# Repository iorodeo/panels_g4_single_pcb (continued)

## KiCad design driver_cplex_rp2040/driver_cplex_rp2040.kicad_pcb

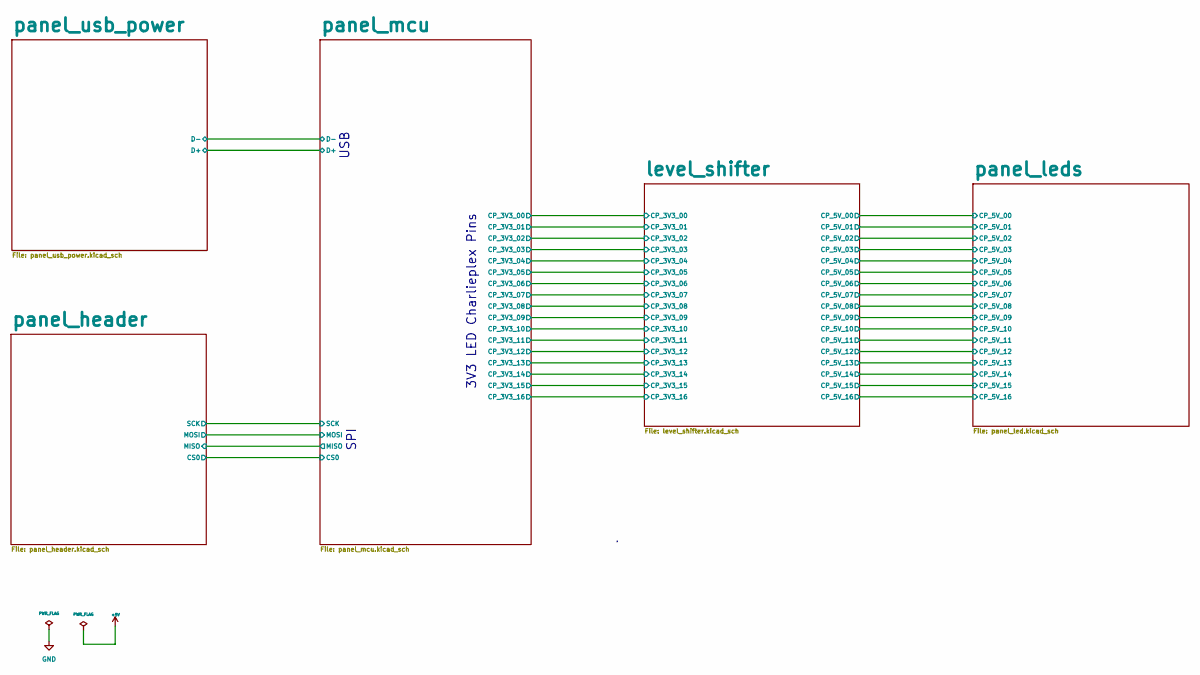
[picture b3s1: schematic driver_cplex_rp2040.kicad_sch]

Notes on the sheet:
SPI
USB
3V3 LED Charlieplex Pins

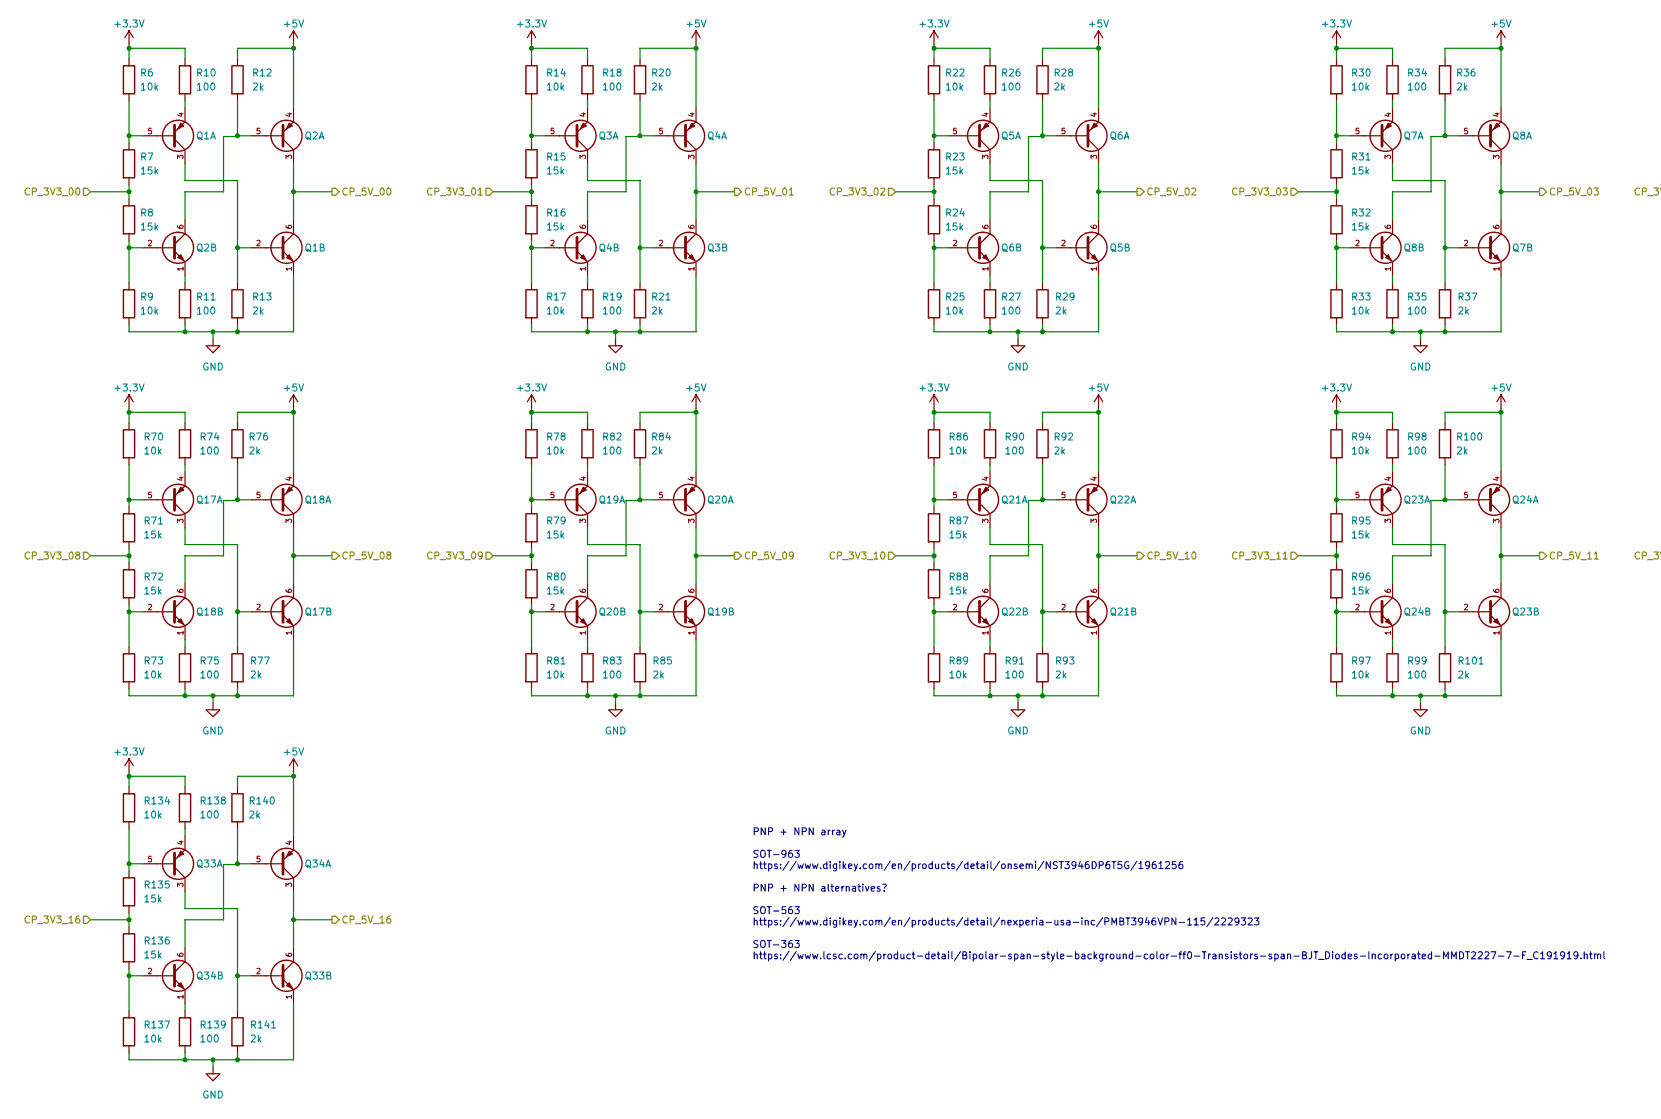
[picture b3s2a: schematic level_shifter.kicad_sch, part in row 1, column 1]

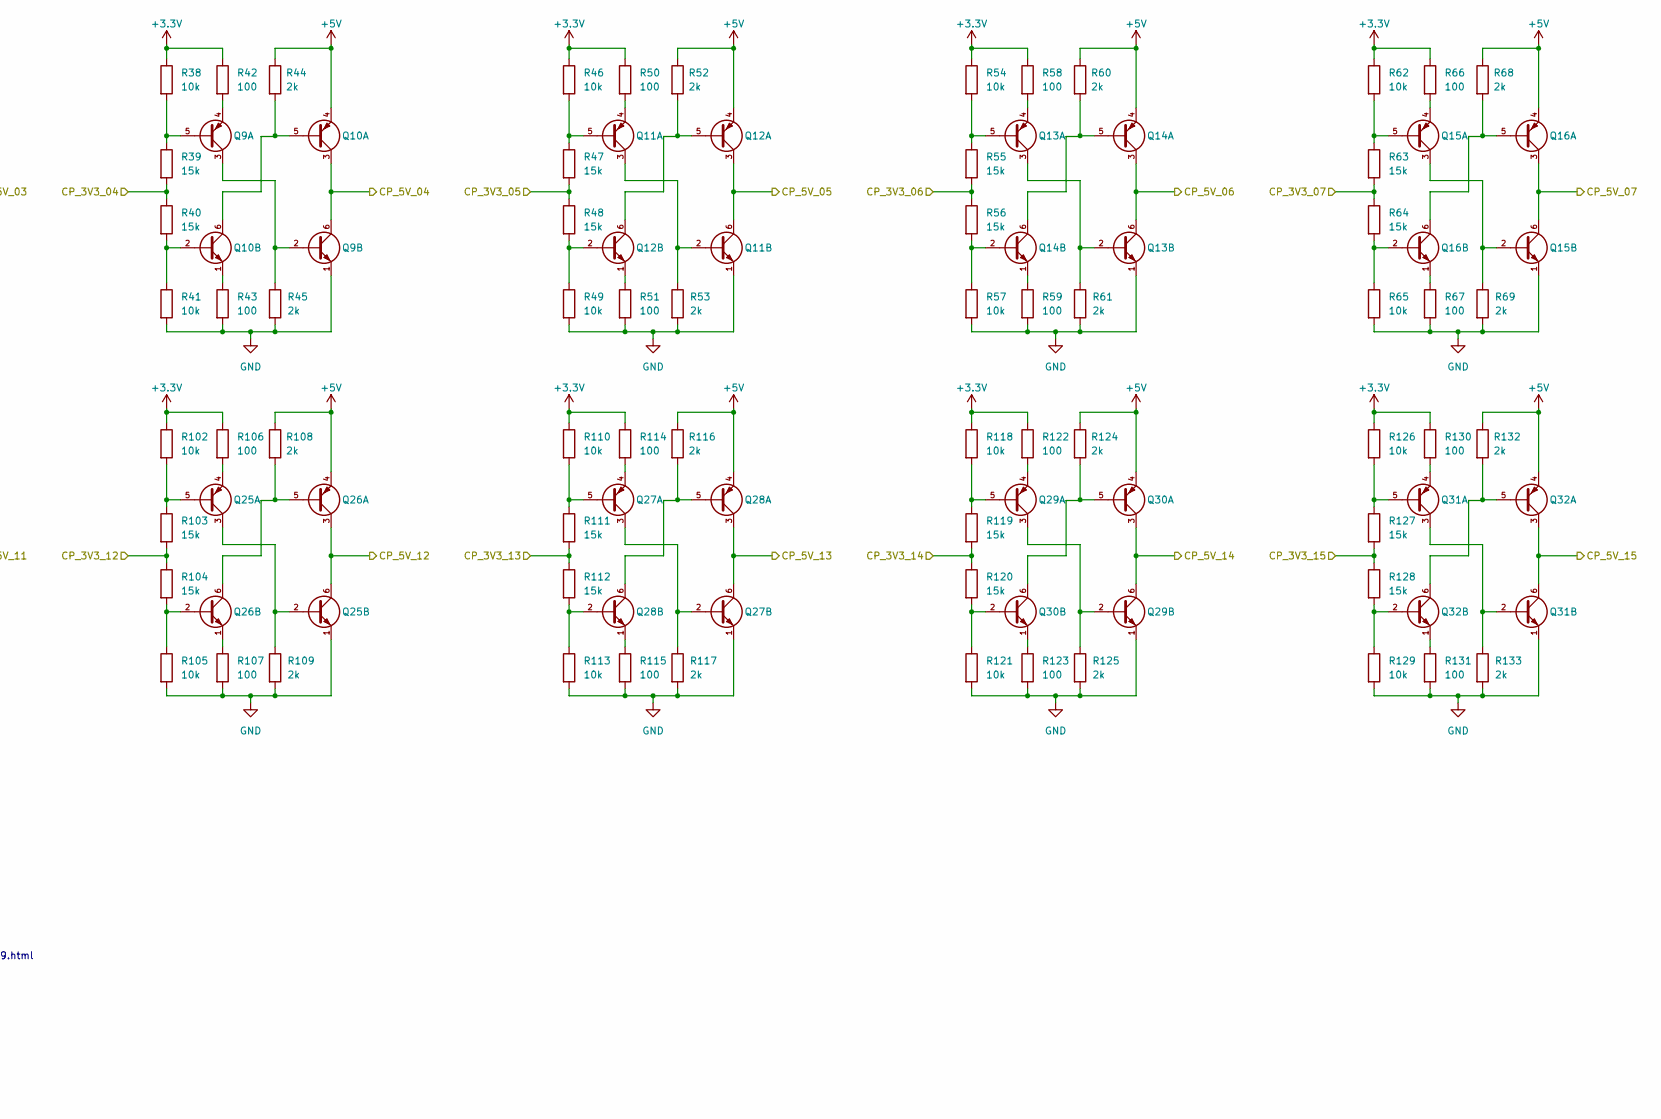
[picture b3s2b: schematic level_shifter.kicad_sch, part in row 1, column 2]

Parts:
Q1, Q2, Q3, Q4, Q5, Q6, Q7, Q8, Q9, Q10, Q11, Q12, Q13, Q14, Q15, Q16, Q17, Q18, Q19, Q20, Q21, Q22, Q23, Q24, Q25, Q26, Q27, Q28, Q29, Q30, Q31, Q32, Q33, Q34: 1xPNP and 1xNPN; SOT-963
R6, R9, R14, R17, R22, R25, R30, R33, R38, R41, R46, R49, R54, R57, R62, R65, R70, R73, R78, R81, R86, R89, R94, R97, R102, R105, R110, R113, R118, R121, R126, R129, R134, R137: 10k; R_0201_0603Metric
R7, R8, R15, R16, R23, R24, R31, R32, R39, R40, R47, R48, R55, R56, R63, R64, R71, R72, R79, R80, R87, R88, R95, R96, R103, R104, R111, R112, R119, R120, R127, R128, R135, R136: 15k; R_0201_0603Metric
R10, R11, R18, R19, R26, R27, R34, R35, R42, R43, R50, R51, R58, R59, R66, R67, R74, R75, R82, R83, R90, R91, R98, R99, R106, R107, R114, R115, R122, R123, R130, R131, R138, R139: 100; R_0201_0603Metric
R12, R13, R20, R21, R28, R29, R36, R37, R44, R45, R52, R53, R60, R61, R68, R69, R76, R77, R84, R85, R92, R93, R100, R101, R108, R109, R116, R117, R124, R125, R132, R133, R140, R141: 2k; R_0201_0603Metric

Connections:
+3.3V: R6.1, R10.1, R14.1, R18.1, R22.1, R26.1, R30.1, R34.1, R38.1, R42.1, R46.1, R50.1, R54.1, R58.1, R62.1, R66.1, R70.1, R74.1, R78.1, R82.1, R86.1, R90.1, R94.1, R98.1, R102.1, R106.1, R110.1, R114.1, R118.1, R122.1, R126.1, R130.1, R134.1, R138.1; also elsewhere on the board
+5V: Q2.4, Q4.4, Q6.4, Q8.4, Q10.4, Q12.4, Q14.4, Q16.4, Q18.4, Q20.4, Q22.4, Q24.4, Q26.4, Q28.4, Q30.4, Q32.4, Q34.4, R12.1, R20.1, R28.1, R36.1, R44.1, R52.1, R60.1, R68.1, R76.1, R84.1, R92.1, R100.1, R108.1, R116.1, R124.1, R132.1, R140.1; also elsewhere on the board
/level_shifter/CP_3V3_00: R7.2, R8.1; also elsewhere on the board
/level_shifter/CP_3V3_01: R15.2, R16.1; also elsewhere on the board
/level_shifter/CP_3V3_02: R23.2, R24.1; also elsewhere on the board
/level_shifter/CP_3V3_03: R31.2, R32.1; also elsewhere on the board
/level_shifter/CP_3V3_04: R39.2, R40.1; also elsewhere on the board
/level_shifter/CP_3V3_05: R47.2, R48.1; also elsewhere on the board
/level_shifter/CP_3V3_06: R55.2, R56.1; also elsewhere on the board
/level_shifter/CP_3V3_07: R63.2, R64.1; also elsewhere on the board
/level_shifter/CP_3V3_08: R71.2, R72.1; also elsewhere on the board
/level_shifter/CP_3V3_09: R79.2, R80.1; also elsewhere on the board
/level_shifter/CP_3V3_10: R87.2, R88.1; also elsewhere on the board
/level_shifter/CP_3V3_11: R95.2, R96.1; also elsewhere on the board
/level_shifter/CP_3V3_12: R103.2, R104.1; also elsewhere on the board
/level_shifter/CP_3V3_13: R111.2, R112.1; also elsewhere on the board
/level_shifter/CP_3V3_14: R119.2, R120.1; also elsewhere on the board
/level_shifter/CP_3V3_15: R127.2, R128.1; also elsewhere on the board
/level_shifter/CP_3V3_16: R135.2, R136.1; also elsewhere on the board
/level_shifter/CP_5V_00: Q1.6, Q2.3; also elsewhere on the board
/level_shifter/CP_5V_01: Q3.6, Q4.3; also elsewhere on the board
/level_shifter/CP_5V_02: Q5.6, Q6.3; also elsewhere on the board
/level_shifter/CP_5V_03: Q7.6, Q8.3; also elsewhere on the board
/level_shifter/CP_5V_04: Q9.6, Q10.3; also elsewhere on the board
/level_shifter/CP_5V_05: Q11.6, Q12.3; also elsewhere on the board
/level_shifter/CP_5V_06: Q13.6, Q14.3; also elsewhere on the board
/level_shifter/CP_5V_07: Q15.6, Q16.3; also elsewhere on the board
/level_shifter/CP_5V_08: Q17.6, Q18.3; also elsewhere on the board
/level_shifter/CP_5V_09: Q19.6, Q20.3; also elsewhere on the board
/level_shifter/CP_5V_10: Q21.6, Q22.3; also elsewhere on the board
/level_shifter/CP_5V_11: Q23.6, Q24.3; also elsewhere on the board
/level_shifter/CP_5V_12: Q25.6, Q26.3; also elsewhere on the board
/level_shifter/CP_5V_13: Q27.6, Q28.3; also elsewhere on the board
/level_shifter/CP_5V_14: Q29.6, Q30.3; also elsewhere on the board
/level_shifter/CP_5V_15: Q31.6, Q32.3; also elsewhere on the board
/level_shifter/CP_5V_16: Q33.6, Q34.3; also elsewhere on the board
GND: Q1.1, Q3.1, Q5.1, Q7.1, Q9.1, Q11.1, Q13.1, Q15.1, Q17.1, Q19.1, Q21.1, Q23.1, Q25.1, Q27.1, Q29.1, Q31.1, Q33.1, R9.2, R11.2, R13.2, R17.2, R19.2, R21.2, R25.2, R27.2, R29.2, R33.2, R35.2, R37.2, R41.2, R43.2, R45.2, R49.2, R51.2, R53.2, R57.2, R59.2, R61.2, R65.2, R67.2, R69.2, R73.2, R75.2, R77.2, R81.2, R83.2, R85.2, R89.2, R91.2, R93.2, R97.2, R99.2, R101.2, R105.2, R107.2, R109.2, R113.2, R115.2, R117.2, R121.2, R123.2, R125.2, R129.2, R131.2, R133.2, R137.2, R139.2, R141.2; also elsewhere on the board
unnamed: Q1.2, Q1.3, R13.1
unnamed: Q1.4, R10.2
unnamed: Q1.5, R6.2, R7.1
unnamed: Q2.1, R11.1
unnamed: Q2.2, R8.2, R9.1
unnamed: Q2.5, Q2.6, R12.2
unnamed: Q3.2, Q3.3, R21.1
unnamed: Q3.4, R18.2
unnamed: Q3.5, R14.2, R15.1
unnamed: Q4.1, R19.1
unnamed: Q4.2, R16.2, R17.1
unnamed: Q4.5, Q4.6, R20.2
unnamed: Q5.2, Q5.3, R29.1
unnamed: Q5.4, R26.2
unnamed: Q5.5, R22.2, R23.1
unnamed: Q6.1, R27.1
unnamed: Q6.2, R24.2, R25.1
unnamed: Q6.5, Q6.6, R28.2
unnamed: Q7.2, Q7.3, R37.1
unnamed: Q7.4, R34.2
unnamed: Q7.5, R30.2, R31.1
unnamed: Q8.1, R35.1
unnamed: Q8.2, R32.2, R33.1
unnamed: Q8.5, Q8.6, R36.2
unnamed: Q9.2, Q9.3, R45.1
unnamed: Q9.4, R42.2
unnamed: Q9.5, R38.2, R39.1
unnamed: Q10.1, R43.1
unnamed: Q10.2, R40.2, R41.1
unnamed: Q10.5, Q10.6, R44.2
unnamed: Q11.2, Q11.3, R53.1
unnamed: Q11.4, R50.2
unnamed: Q11.5, R46.2, R47.1
unnamed: Q12.1, R51.1
unnamed: Q12.2, R48.2, R49.1
unnamed: Q12.5, Q12.6, R52.2
unnamed: Q13.2, Q13.3, R61.1
unnamed: Q13.4, R58.2
unnamed: Q13.5, R54.2, R55.1
unnamed: Q14.1, R59.1
unnamed: Q14.2, R56.2, R57.1
unnamed: Q14.5, Q14.6, R60.2
unnamed: Q15.2, Q15.3, R69.1
unnamed: Q15.4, R66.2
unnamed: Q15.5, R62.2, R63.1
unnamed: Q16.1, R67.1
unnamed: Q16.2, R64.2, R65.1
unnamed: Q16.5, Q16.6, R68.2
unnamed: Q17.2, Q17.3, R77.1
unnamed: Q17.4, R74.2
unnamed: Q17.5, R70.2, R71.1
unnamed: Q18.1, R75.1
unnamed: Q18.2, R72.2, R73.1
unnamed: Q18.5, Q18.6, R76.2
unnamed: Q19.2, Q19.3, R85.1
unnamed: Q19.4, R82.2
unnamed: Q19.5, R78.2, R79.1
unnamed: Q20.1, R83.1
unnamed: Q20.2, R80.2, R81.1
unnamed: Q20.5, Q20.6, R84.2
unnamed: Q21.2, Q21.3, R93.1
unnamed: Q21.4, R90.2
unnamed: Q21.5, R86.2, R87.1
unnamed: Q22.1, R91.1
unnamed: Q22.2, R88.2, R89.1
unnamed: Q22.5, Q22.6, R92.2
unnamed: Q23.2, Q23.3, R101.1
unnamed: Q23.4, R98.2
unnamed: Q23.5, R94.2, R95.1
unnamed: Q24.1, R99.1
unnamed: Q24.2, R96.2, R97.1
unnamed: Q24.5, Q24.6, R100.2
unnamed: Q25.2, Q25.3, R109.1
unnamed: Q25.4, R106.2
unnamed: Q25.5, R102.2, R103.1
unnamed: Q26.1, R107.1
unnamed: Q26.2, R104.2, R105.1
unnamed: Q26.5, Q26.6, R108.2
unnamed: Q27.2, Q27.3, R117.1
unnamed: Q27.4, R114.2
unnamed: Q27.5, R110.2, R111.1
unnamed: Q28.1, R115.1
unnamed: Q28.2, R112.2, R113.1
unnamed: Q28.5, Q28.6, R116.2
unnamed: Q29.2, Q29.3, R125.1
unnamed: Q29.4, R122.2
unnamed: Q29.5, R118.2, R119.1
unnamed: Q30.1, R123.1
unnamed: Q30.2, R120.2, R121.1
unnamed: Q30.5, Q30.6, R124.2
unnamed: Q31.2, Q31.3, R133.1
unnamed: Q31.4, R130.2
unnamed: Q31.5, R126.2, R127.1
unnamed: Q32.1, R131.1
unnamed: Q32.2, R128.2, R129.1
unnamed: Q32.5, Q32.6, R132.2
unnamed: Q33.2, Q33.3, R141.1
unnamed: Q33.4, R138.2
unnamed: Q33.5, R134.2, R135.1
unnamed: Q34.1, R139.1
unnamed: Q34.2, R136.2, R137.1
unnamed: Q34.5, Q34.6, R140.2

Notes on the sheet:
PNP + NPN array SOT-963 https://www.digikey.com/en/products/detail/onsemi/NST3946DP6T5G/1961256 PNP + NPN alternatives? SOT-563 https://www.digikey.com/en/products/detail/nexperia-usa-inc/PMBT3946VPN-115/2229323 SOT-363 https://www.lcsc.com/product-detail/Bipolar-span-style-background-color-ff0-Tra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

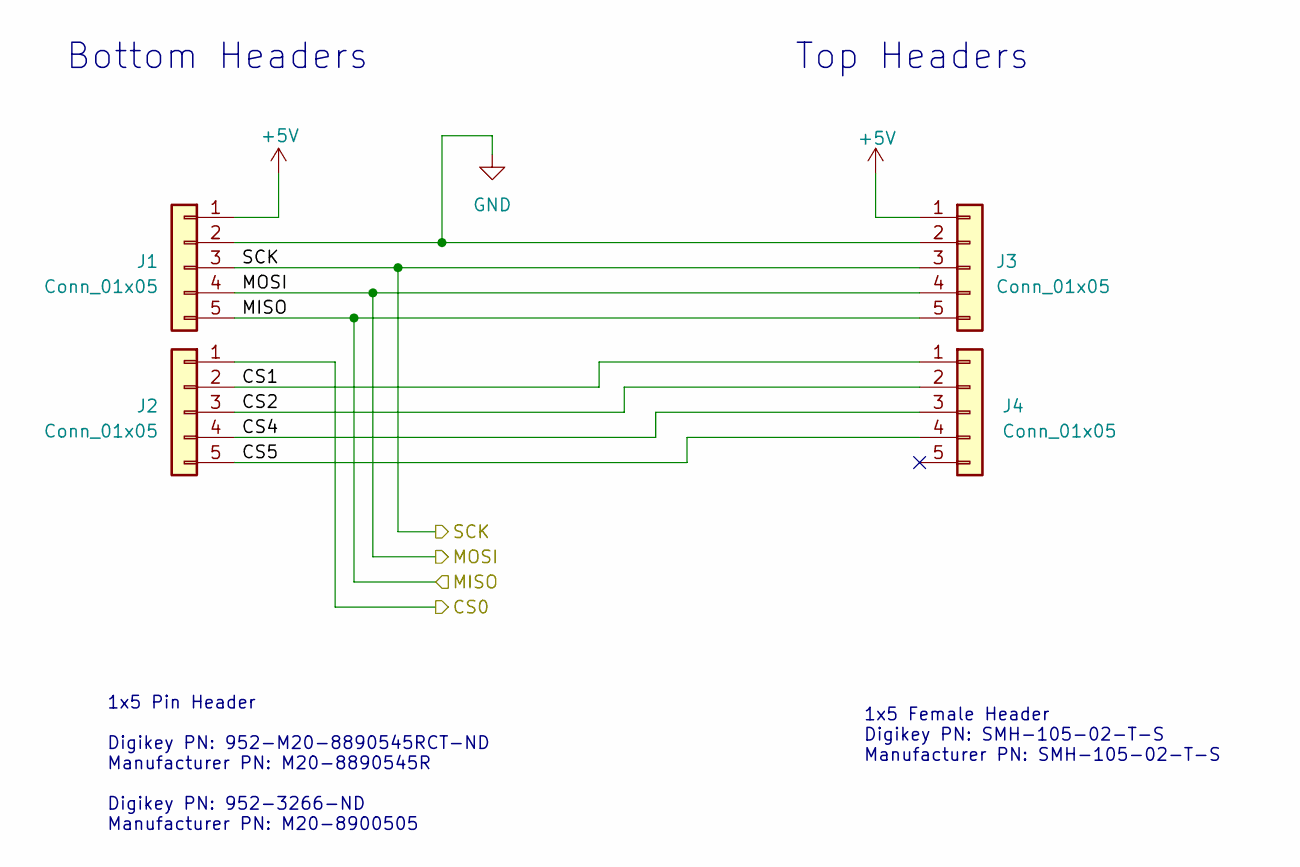
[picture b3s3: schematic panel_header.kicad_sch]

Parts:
J1, J2: Conn_01x05; PinHeader_1x5_M20-8890545R
J3, J4: Conn_01x05; C_0402_1005Metric

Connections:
+5V: J1.5, J3.5; also elsewhere on the board
/panel_header/MISO: J1.1, J3.1; also elsewhere on the board
/panel_header/MOSI: J1.2, J3.2; also elsewhere on the board
/panel_header/SCK: J1.3, J3.3; also elsewhere on the board
GND: J1.4, J3.4; also elsewhere on the board

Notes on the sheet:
1x5 Female Header Digikey PN: SMH-105-02-T-S Manufacturer PN: SMH-105-02-T-S
Bottom Headers
1x5 Pin Header Digikey PN: 952-M20-8890545RCT-ND Manufacturer PN: M20-8890545R Digikey PN: 952-3266-ND Manufacturer PN: M20-8900505
Top Headers

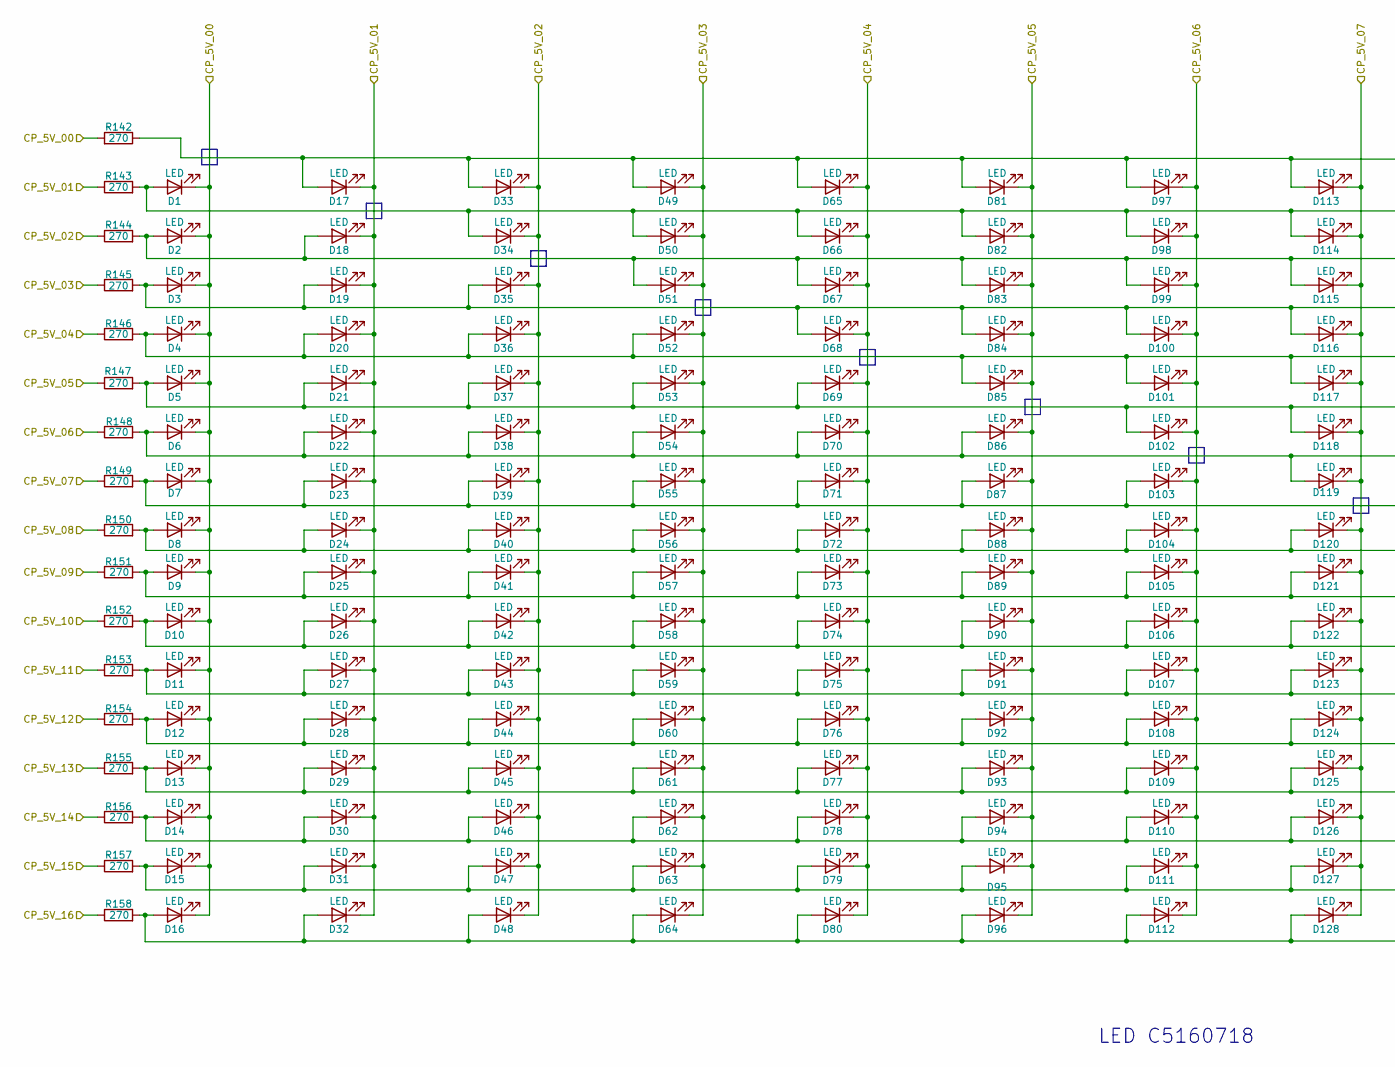
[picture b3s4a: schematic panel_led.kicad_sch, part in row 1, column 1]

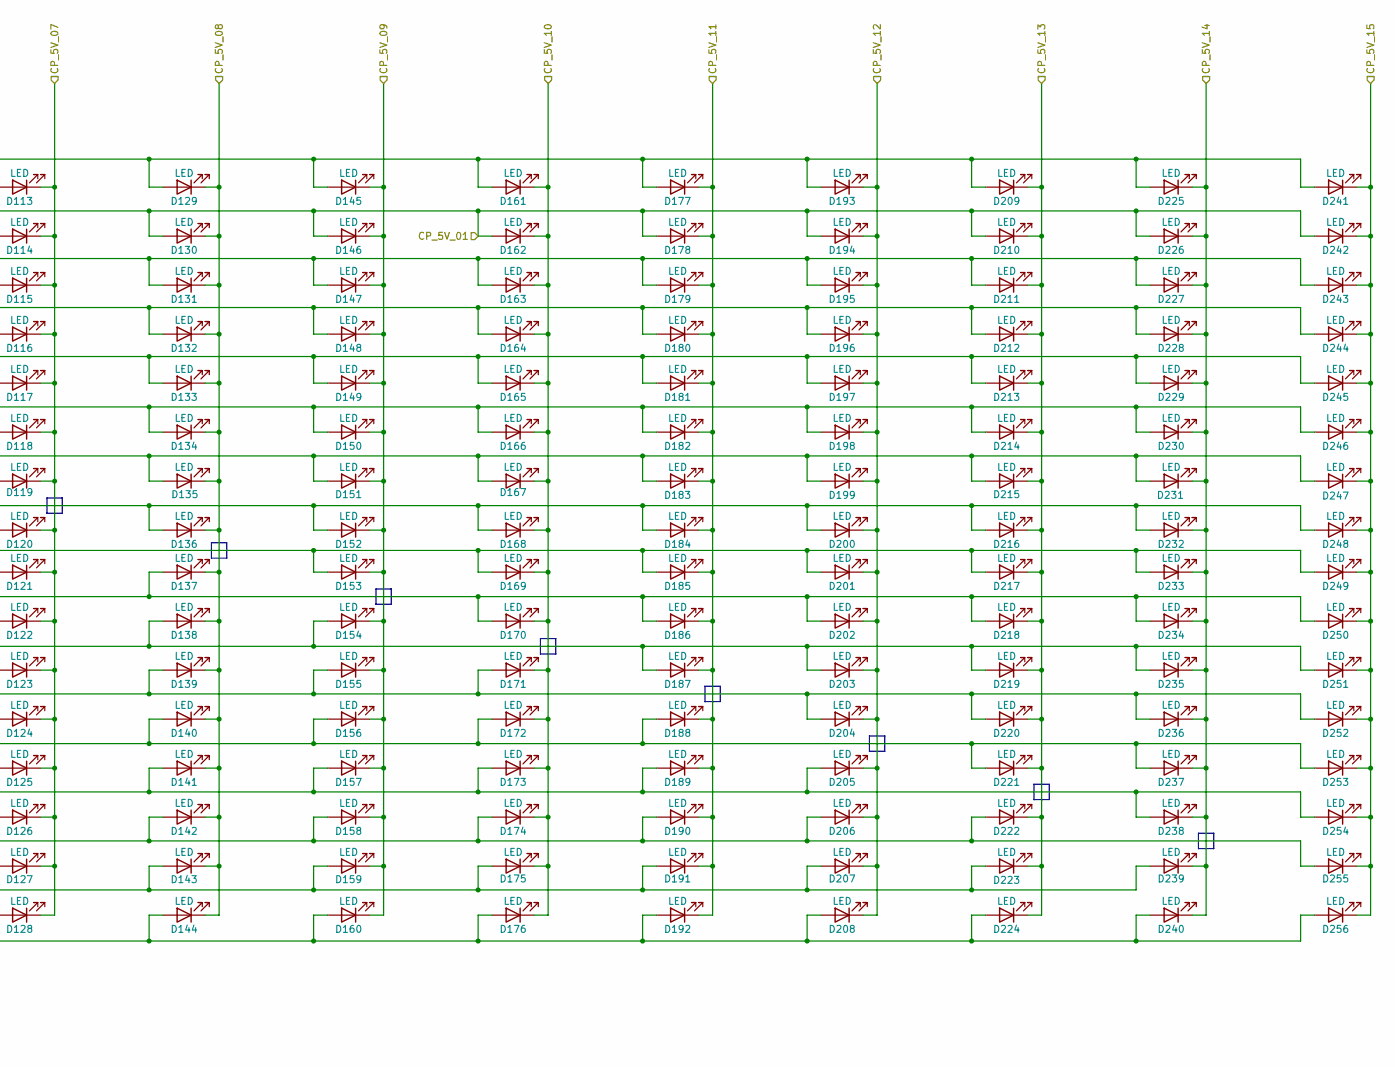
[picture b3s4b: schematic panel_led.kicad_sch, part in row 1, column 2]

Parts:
D1, D2, D3, D4, D5, D6, D7, D8, D9, D10, D11, D12, D13, D14, D15, D16, D17, D18, D19, D20, D21, D22, D23, D24, D25, D26, D27, D28, D29, D30, D31, D32, D33, D34, D35, D36, D37, D38, D39, D40, D41, D42, D43, D44, D45, D46, D47, D48, D49, D50, D51, D52, D53, D54, D55, D56, D57, D58, D59, D60, D61, D62, D63, D64, D65, D66, D67, D68, D69, D70, D71, D72, D73, D74, D75, D76, D77, D78, D79, D80, D81, D82, D83, D84, D85, D86, D87, D88, D89, D90, D91, D92, D93, D94, D95, D96, D97, D98, D99, D100, D101, D102, D103, D104, D105, D106, D107, D108, D109, D110, D111, D112, D113, D114, D115, D116, D117, D118, D119, D120, D121, D122, D123, D124, D125, D126, D127, D128, D129, D130, D131, D132, D133, D134, D135, D136, D137, D138, D139, D140, D141, D142, D143, D144, D145, D146, D147, D148, D149, D150, D151, D152, D153, D154, D155, D156, D157, D158, D159, D160, D161, D162, D163, D164, D165, D166, D167, D168, D169, D170, D171, D172, D173, D174, D175, D176, D177, D178, D179, D180, D181, D182, D183, D184, D185, D186, D187, D188, D189, D190, D191, D192, D193, D194, D195, D196, D197, D198, D199, D200, D201, D202, D203, D204, D205, D206, D207, D208, D209, D210, D211, D212, D213, D214, D215, D216, D217, D218, D219, D220, D221, D222, D223, D224, D225, D226, D227, D228, D229, D230, D231, D232, D233, D234, D235, D236, D237, D238, D239, D240, D241, D242, D243, D244, D245, D246, D247, D248, D249, D250, D251, D252, D253, D254, D255, D256: LED; LED_0402_1005Metric
R142, R143, R144, R145, R146, R147, R148, R149, R150, R151, R152, R153, R154, R155, R156, R157, R158: 270; R_0201_0603Metric

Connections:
/level_shifter/CP_5V_00: D1.1 (K), D2.1 (K), D3.1 (K), D4.1 (K), D5.1 (K), D6.1 (K), D7.1 (K), D8.1 (K), D9.1 (K), D10.1 (K), D11.1 (K), D12.1 (K), D13.1 (K), D14.1 (K), D15.1 (K), D16.1 (K), R142.2; also elsewhere on the board
/level_shifter/CP_5V_01: D1.2 (A), D17.1 (K), D18.1 (K), D19.1 (K), D20.1 (K), D21.1 (K), D22.1 (K), D23.1 (K), D24.1 (K), D25.1 (K), D26.1 (K), D27.1 (K), D28.1 (K), D29.1 (K), D30.1 (K), D31.1 (K), D32.1 (K), D34.2 (A), D50.2 (A), D66.2 (A), D82.2 (A), D98.2 (A), D114.2 (A), D130.2 (A), D146.2 (A), D162.2 (A), D178.2 (A), D194.2 (A), D210.2 (A), D226.2 (A), D242.2 (A), R143.1, R143.2; also elsewhere on the board
/level_shifter/CP_5V_02: D33.1 (K), D34.1 (K), D35.1 (K), D36.1 (K), D37.1 (K), D38.1 (K), D39.1 (K), D40.1 (K), D41.1 (K), D42.1 (K), D43.1 (K), D44.1 (K), D45.1 (K), D46.1 (K), D47.1 (K), D48.1 (K), R144.1; also elsewhere on the board
/level_shifter/CP_5V_03: D49.1 (K), D50.1 (K), D51.1 (K), D52.1 (K), D53.1 (K), D54.1 (K), D55.1 (K), D56.1 (K), D57.1 (K), D58.1 (K), D59.1 (K), D60.1 (K), D61.1 (K), D62.1 (K), D63.1 (K), D64.1 (K), R145.1; also elsewhere on the board
/level_shifter/CP_5V_04: D65.1 (K), D66.1 (K), D67.1 (K), D68.1 (K), D69.1 (K), D70.1 (K), D71.1 (K), D72.1 (K), D73.1 (K), D74.1 (K), D75.1 (K), D76.1 (K), D77.1 (K), D78.1 (K), D79.1 (K), D80.1 (K), R146.1; also elsewhere on the board
/level_shifter/CP_5V_05: D81.1 (K), D82.1 (K), D83.1 (K), D84.1 (K), D85.1 (K), D86.1 (K), D87.1 (K), D88.1 (K), D89.1 (K), D90.1 (K), D91.1 (K), D92.1 (K), D93.1 (K), D94.1 (K), D95.1 (K), D96.1 (K), R147.1; also elsewhere on the board
/level_shifter/CP_5V_06: D97.1 (K), D98.1 (K), D99.1 (K), D100.1 (K), D101.1 (K), D102.1 (K), D103.1 (K), D104.1 (K), D105.1 (K), D106.1 (K), D107.1 (K), D108.1 (K), D109.1 (K), D110.1 (K), D111.1 (K), D112.1 (K), R148.1; also elsewhere on the board
/level_shifter/CP_5V_07: D113.1 (K), D114.1 (K), D115.1 (K), D116.1 (K), D117.1 (K), D118.1 (K), D119.1 (K), D120.1 (K), D121.1 (K), D122.1 (K), D123.1 (K), D124.1 (K), D125.1 (K), D126.1 (K), D127.1 (K), D128.1 (K), R149.1; also elsewhere on the board
/level_shifter/CP_5V_08: D129.1 (K), D130.1 (K), D131.1 (K), D132.1 (K), D133.1 (K), D134.1 (K), D135.1 (K), D136.1 (K), D137.1 (K), D138.1 (K), D139.1 (K), D140.1 (K), D141.1 (K), D142.1 (K), D143.1 (K), D144.1 (K), R150.1; also elsewhere on the board
/level_shifter/CP_5V_09: D145.1 (K), D146.1 (K), D147.1 (K), D148.1 (K), D149.1 (K), D150.1 (K), D151.1 (K), D152.1 (K), D153.1 (K), D154.1 (K), D155.1 (K), D156.1 (K), D157.1 (K), D158.1 (K), D159.1 (K), D160.1 (K), R151.1; also elsewhere on the board
/level_shifter/CP_5V_10: D161.1 (K), D162.1 (K), D163.1 (K), D164.1 (K), D165.1 (K), D166.1 (K), D167.1 (K), D168.1 (K), D169.1 (K), D170.1 (K), D171.1 (K), D172.1 (K), D173.1 (K), D174.1 (K), D175.1 (K), D176.1 (K), R152.1; also elsewhere on the board
/level_shifter/CP_5V_11: D177.1 (K), D178.1 (K), D179.1 (K), D180.1 (K), D181.1 (K), D182.1 (K), D183.1 (K), D184.1 (K), D185.1 (K), D186.1 (K), D187.1 (K), D188.1 (K), D189.1 (K), D190.1 (K), D191.1 (K), D192.1 (K), R153.1; also elsewhere on the board
/level_shifter/CP_5V_12: D193.1 (K), D194.1 (K), D195.1 (K), D196.1 (K), D197.1 (K), D198.1 (K), D199.1 (K), D200.1 (K), D201.1 (K), D202.1 (K), D203.1 (K), D204.1 (K), D205.1 (K), D206.1 (K), D207.1 (K), D208.1 (K), R154.1; also elsewhere on the board
/level_shifter/CP_5V_13: D209.1 (K), D210.1 (K), D211.1 (K), D212.1 (K), D213.1 (K), D214.1 (K), D215.1 (K), D216.1 (K), D217.1 (K), D218.1 (K), D219.1 (K), D220.1 (K), D221.1 (K), D222.1 (K), D223.1 (K), D224.1 (K), R155.1; also elsewhere on the board
/level_shifter/CP_5V_14: D225.1 (K), D226.1 (K), D227.1 (K), D228.1 (K), D229.1 (K), D230.1 (K), D231.1 (K), D232.1 (K), D233.1 (K), D234.1 (K), D235.1 (K), D236.1 (K), D237.1 (K), D238.1 (K), D239.1 (K), D240.1 (K), R156.1; also elsewhere on the board
/level_shifter/CP_5V_15: D241.1 (K), D242.1 (K), D243.1 (K), D244.1 (K), D245.1 (K), D246.1 (K), D247.1 (K), D248.1 (K), D249.1 (K), D250.1 (K), D251.1 (K), D252.1 (K), D253.1 (K), D254.1 (K), D255.1 (K), D256.1 (K), R157.1; also elsewhere on the board
/level_shifter/CP_5V_16: R158.1; also elsewhere on the board
unnamed: D10.2 (A), D26.2 (A), D42.2 (A), D58.2 (A), D74.2 (A), D90.2 (A), D106.2 (A), D122.2 (A), D138.2 (A), D154.2 (A), D187.2 (A), D203.2 (A), D219.2 (A), D235.2 (A), D251.2 (A), R152.2
unnamed: D3.2 (A), D19.2 (A), D35.2 (A), D68.2 (A), D84.2 (A), D100.2 (A), D116.2 (A), D132.2 (A), D148.2 (A), D164.2 (A), D180.2 (A), D196.2 (A), D212.2 (A), D228.2 (A), D244.2 (A), R145.2
unnamed: D4.2 (A), D20.2 (A), D36.2 (A), D52.2 (A), D85.2 (A), D101.2 (A), D117.2 (A), D133.2 (A), D149.2 (A), D165.2 (A), D181.2 (A), D197.2 (A), D213.2 (A), D229.2 (A), D245.2 (A), R146.2
unnamed: D5.2 (A), D21.2 (A), D37.2 (A), D53.2 (A), D69.2 (A), D102.2 (A), D118.2 (A), D134.2 (A), D150.2 (A), D166.2 (A), D182.2 (A), D198.2 (A), D214.2 (A), D230.2 (A), D246.2 (A), R147.2
unnamed: D7.2 (A), D23.2 (A), D39.2 (A), D55.2 (A), D71.2 (A), D87.2 (A), D103.2 (A), D136.2 (A), D152.2 (A), D168.2 (A), D184.2 (A), D200.2 (A), D216.2 (A), D232.2 (A), D248.2 (A), R149.2
unnamed: D8.2 (A), D24.2 (A), D40.2 (A), D56.2 (A), D72.2 (A), D88.2 (A), D104.2 (A), D120.2 (A), D153.2 (A), D169.2 (A), D185.2 (A), D201.2 (A), D217.2 (A), D233.2 (A), D249.2 (A), R150.2
unnamed: D9.2 (A), D25.2 (A), D41.2 (A), D57.2 (A), D73.2 (A), D89.2 (A), D105.2 (A), D121.2 (A), D137.2 (A), D170.2 (A), D186.2 (A), D202.2 (A), D218.2 (A), D234.2 (A), D250.2 (A), R151.2
unnamed: D11.2 (A), D27.2 (A), D43.2 (A), D59.2 (A), D75.2 (A), D91.2 (A), D107.2 (A), D123.2 (A), D139.2 (A), D155.2 (A), D171.2 (A), D204.2 (A), D220.2 (A), D236.2 (A), D252.2 (A), R153.2
unnamed: D12.2 (A), D28.2 (A), D44.2 (A), D60.2 (A), D76.2 (A), D92.2 (A), D108.2 (A), D124.2 (A), D140.2 (A), D156.2 (A), D172.2 (A), D188.2 (A), D221.2 (A), D237.2 (A), D253.2 (A), R154.2
unnamed: D13.2 (A), D29.2 (A), D45.2 (A), D61.2 (A), D77.2 (A), D93.2 (A), D109.2 (A), D125.2 (A), D141.2 (A), D157.2 (A), D173.2 (A), D189.2 (A), D205.2 (A), D238.2 (A), D254.2 (A), R155.2
unnamed: D14.2 (A), D30.2 (A), D46.2 (A), D62.2 (A), D78.2 (A), D94.2 (A), D110.2 (A), D126.2 (A), D142.2 (A), D158.2 (A), D174.2 (A), D190.2 (A), D206.2 (A), D222.2 (A), D255.2 (A), R156.2
unnamed: D15.2 (A), D31.2 (A), D47.2 (A), D63.2 (A), D79.2 (A), D95.2 (A), D111.2 (A), D127.2 (A), D143.2 (A), D159.2 (A), D175.2 (A), D191.2 (A), D207.2 (A), D223.2 (A), D239.2 (A), R157.2
unnamed: D16.2 (A), D32.2 (A), D48.2 (A), D64.2 (A), D80.2 (A), D96.2 (A), D112.2 (A), D128.2 (A), D144.2 (A), D160.2 (A), D176.2 (A), D192.2 (A), D208.2 (A), D224.2 (A), D240.2 (A), D256.2 (A), R158.2
unnamed: D17.2 (A), D33.2 (A), D49.2 (A), D65.2 (A), D81.2 (A), D97.2 (A), D113.2 (A), D129.2 (A), D145.2 (A), D161.2 (A), D177.2 (A), D193.2 (A), D209.2 (A), D225.2 (A), D241.2 (A), R142.1
unnamed: D2.2 (A), D18.2 (A), D51.2 (A), D67.2 (A), D83.2 (A), D99.2 (A), D115.2 (A), D131.2 (A), D147.2 (A), D163.2 (A), D179.2 (A), D195.2 (A), D211.2 (A), D227.2 (A), D243.2 (A), R144.2
unnamed: D6.2 (A), D22.2 (A), D38.2 (A), D54.2 (A), D70.2 (A), D86.2 (A), D119.2 (A), D135.2 (A), D151.2 (A), D167.2 (A), D183.2 (A), D199.2 (A), D215.2 (A), D231.2 (A), D247.2 (A), R148.2

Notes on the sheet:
LED C5160718
